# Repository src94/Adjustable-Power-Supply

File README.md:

# Adjustable-Power-Supply
CC-CV.
Output Voltage can be varied from 7.8V to 39V.
Output Current can be varied from 0 to 5A.
The power supply can be used to charge a 9S battery pack (Li-ion) at 0 to 5A.

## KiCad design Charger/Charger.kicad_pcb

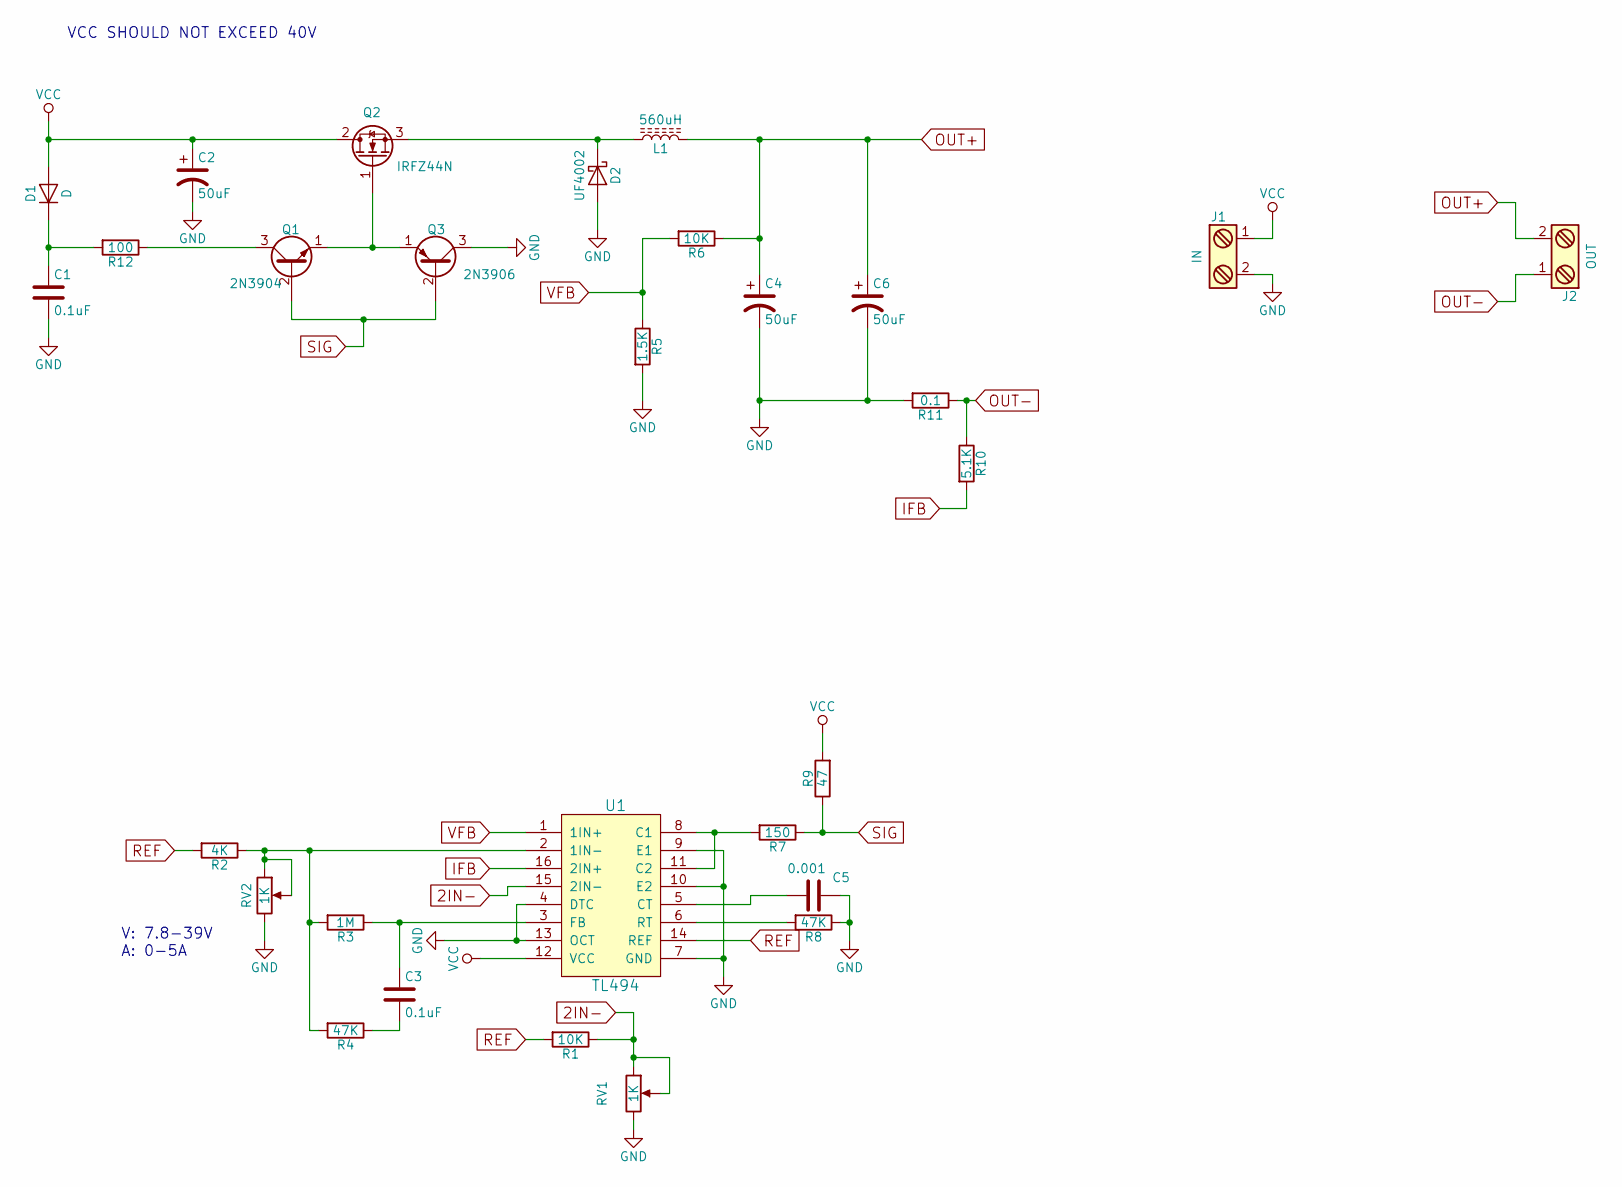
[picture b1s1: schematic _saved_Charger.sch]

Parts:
C1, C3: 0.1uF; C_Disc_D3.8mm_W2.6mm_P2.50mm
C2, C4, C6: 50uF; CP_Radial_D4.0mm_P1.50mm
C5: 0.001; C_Disc_D3.8mm_W2.6mm_P2.50mm
D1: D; D_A-405_P10.16mm_Horizontal
D2: UF4002; D_A-405_P10.16mm_Horizontal
J1: IN; TerminalBlock_Pheonix_MKDS1.5-2pol
J2: OUT; TerminalBlock_Pheonix_MKDS1.5-2pol
L1: 560uH; L_Toroid_Vertical_L31.8mm_W15.9mm_P13.50mm_Bourns_5700
Q1: 2N3904; TO-92_Inline_Narrow_Oval
Q2: IRFZ44N; TO-220_Vertical
Q3: 2N3906; TO-92_Inline_Narrow_Oval
R1, R6: 10K; R_Axial_DIN0207_L6.3mm_D2.5mm_P7.62mm_Horizontal
R2: 4K; R_Axial_DIN0207_L6.3mm_D2.5mm_P7.62mm_Horizontal
R3: 1M; R_Axial_DIN0207_L6.3mm_D2.5mm_P7.62mm_Horizontal
R4, R8: 47K; R_Axial_DIN0207_L6.3mm_D2.5mm_P7.62mm_Horizontal
R5: 1.5K; R_Axial_DIN0207_L6.3mm_D2.5mm_P7.62mm_Horizontal
R7: 150; R_Axial_DIN0207_L6.3mm_D2.5mm_P7.62mm_Horizontal
R9: 47; R_Axial_DIN0207_L6.3mm_D2.5mm_P7.62mm_Horizontal
R10: 5.1K; R_Axial_DIN0207_L6.3mm_D2.5mm_P7.62mm_Horizontal
R11: 0.1; R_Axial_DIN0414_L11.9mm_D4.5mm_P15.24mm_Horizontal
R12: 100; R_Axial_DIN0207_L6.3mm_D2.5mm_P7.62mm_Horizontal
RV1, RV2: 1K; Potentiometer_Trimmer_Bourns_3296W
U1: TL494; DIP-16_W7.62mm_LongPads

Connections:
2IN-: R1.1, RV1.1, RV1.2, U1.15 (2IN-)
GND: C1.2, C2.2, C4.2, C5.1, C6.2, D2.2 (A), J1.2, Q3.3 (C), R5.2, R8.1, R11.2, RV1.3, RV2.3, U1.4 (DTC), U1.7 (GND), U1.9 (E1), U1.10 (E2), U1.13 (OCT)
IFB: R10.2, U1.16 (2IN+)
unnamed: C1.1, D1.1 (K), R12.2
unnamed: C3.1, R3.1, U1.3 (FB)
unnamed: C3.2, R4.1
unnamed: C5.2, U1.5 (CT)
unnamed: D2.1 (K), L1.1, Q2.3 (S)
unnamed: Q1.1 (E), Q2.1 (G), Q3.1 (E)
unnamed: Q1.3 (C), R12.1
unnamed: R2.1, R3.2, R4.2, RV2.1, RV2.2, U1.2 (1IN-)
unnamed: R7.2, U1.8 (C1), U1.11 (C2)
unnamed: R8.2, U1.6 (RT)
OUT+: C4.1, C6.1, J2.2, L1.2, R6.1
OUT-: J2.1, R10.1, R11.1
REF: R1.2, R2.2, U1.14 (REF)
SIG: Q1.2 (B), Q3.2 (B), R7.1, R9.1
VCC: C2.1, D1.2 (A), J1.1, Q2.2 (D), R9.2, U1.12 (VCC)
VFB: R5.1, R6.2, U1.1 (1IN+)

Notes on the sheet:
VCC SHOULD NOT EXCEED 40V
V: 7.8-39V A: 0-5A

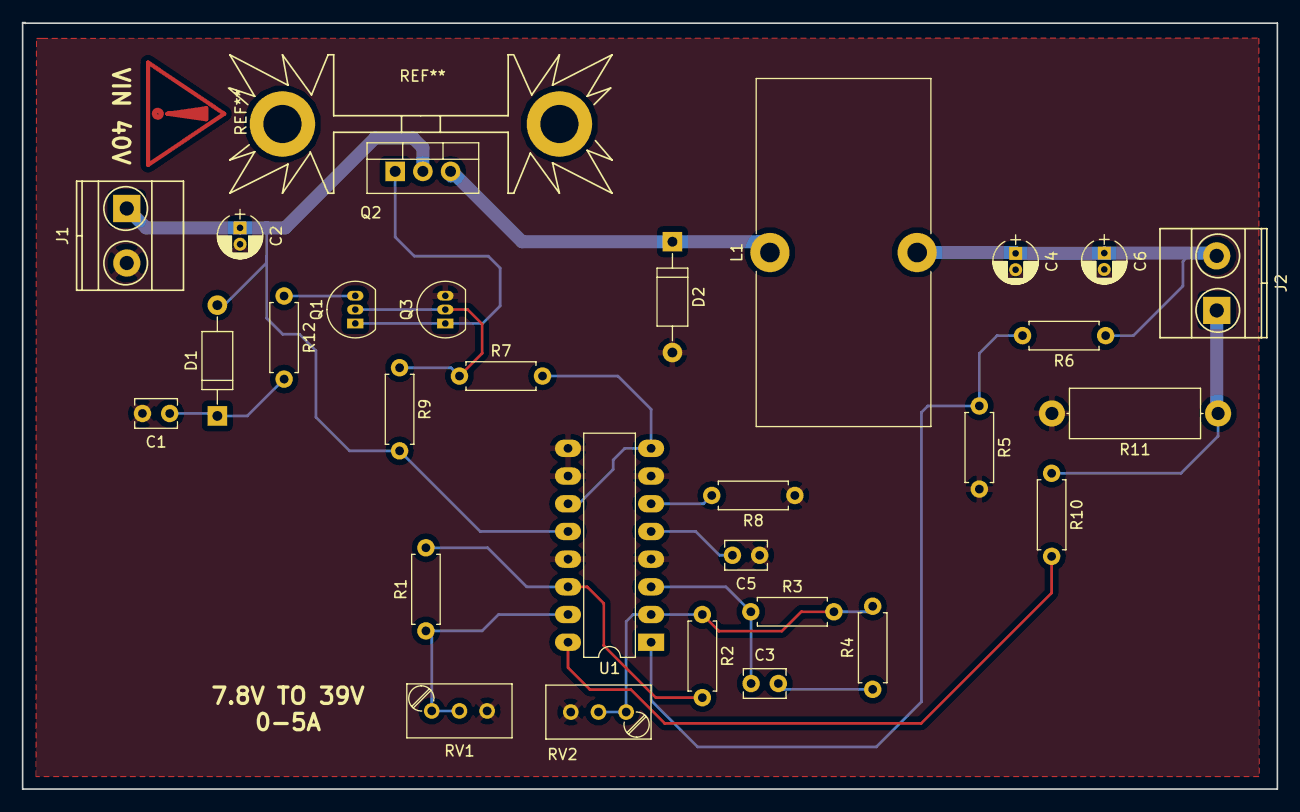
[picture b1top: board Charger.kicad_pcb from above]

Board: 2 copper layers, 115.1 x 70.3 mm, 29 parts (0 on the bottom side), 19 nets.
